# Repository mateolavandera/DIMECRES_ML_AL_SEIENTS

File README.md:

View this project on [CADLAB.io](https://cadlab.io/project/28988). 

# DIMECRES_ML_AL_SEIENTS
## Autors
- Mateo Lavandera Mulet (@mateolavandera)
- Alex Lara Bailon (@AlexLB4)

## Versió - v1.0 ## Curs - Assignatura de Disseny de PCBs amb KiCad - [Curs 2024-2025]

## Objectiu Descripció breu de l'objectiu del projecte.
L’objectiu del nostre projecte és dissenyar un sistema que sigui capaç d'executar correctament les diferents funcions que controlen uns seients elèctrics d’un cotxe qualsevol.

## Requisits i especificacions
→ 3 motors (posició, alçada, reclinació) amb els seus finals de carrera. 
→ Calefacció del seient. 
→ Sensor digital de cinturons. 
→ Memòria externa no volàtil per guardar posicions preprogramades.

## Diagrama de blocs (Afegiu una imatge del diagrama de blocs)
### Tercera versió (final)

## Taula de components
| Descripció | Manufacturer Number | Package | Datasheet | Proveïdor | Unitats |
|------------|--------------------|---------|----------|----------|---------|
| Regulador Lineal 1.5 A  | LD1086V | TO-220 | [Enllaç](https://www.st.com/content/ccc/resource/technical/document/datasheet/53/db/00/58/09/98/4b/36/CD00001884.pdf/files/CD00001884.pdf/jcr:content/translations/en.CD00001884.pdf) | DigiKey | 1 |
| Microcontrolador PIC 8-bit 300mA | PIC18F4580-I/PT | 44-TQFP | [Enllaç](https://ww1.microchip.com/downloads/en/DeviceDoc/39637d.pdf) | DigiKey | 1 |
| DRV Bipolar 4.5-36 V  | L293D | 16-DIP | [Enllaç](https://www.st.com/content/ccc/resource/technical/document/datasheet/04/ac/22/f9/20/5d/43/a1/CD00000059.pdf/files/CD00000059.pdf/jcr:content/translations/en.CD00000059.pdf) | DigiKey | 2 |
| Memòria EEPROM I2C 5 mA  | 24LC512T-I/SN | 8-SOIC | [Enllaç](https://ww1.microchip.com/downloads/en/DeviceDoc/24AA512-24LC512-24FC512-512K-Bit-I2C-Serial-EEPROM-20001754Q.pdf) | DigiKey | 1 |
| Bus CAN (TRANSCEIVER) | TJA1051T	| 8-SOIC | [Enllaç](https://www.nxp.com/docs/en/data-sheet/TJA1051.pdf) | DigiKey | 1 |
| Final de carrera (Comparador) 5 V 4 mA  | LT1721 (Quad) | 16-SOIC | [Enllaç](https://www.analog.com/media/en/technical-documentation/data-sheets/17201fc.pdf) | DigiKey | 1 |
| Condicionador de temperatura (Amplificador) 30 mA  | LT6234 | 16-SSOP | [Enllaç](https://www.analog.com/media/en/technical-documentation/data-sheets/623345fc.pdf) | DigiKey | 1 |
| Sensor de temperatura 60uA | LM35 | 8-SOIC | [Enllaç](https://www.ti.com/lit/ds/symlink/lm35.pdf) | DigiKey | 1 |
| Relé 12mA | Omron G5V-1 | SIP-6 | [Enllaç](https://omronfs.omron.com/en_US/ecb/products/pdf/en-g5v_1.pdf) | DigiKey | 1 |

## Funcionalitats
- [ ] Funció 1
- [ ] Funció 2
- [ ] Funció 3

## Historial de canvis 
| Data | Autor | Branch | Descripció |
|------------|-------|--------|-----------------------------------------------------|
| 2025-03-22 | Alex | `main` | Modificació readme, concretament llistat d'elements |
| 2025-03-22 | Mateo | `main` | Correcció del diagrama de blocs |
| 2025-03-23 | Mateo | `main` | Primera versió de l'esquemàtic  |
| 2025-03-24 | Mateo | `main` | Segona versió de l'esquemàtic  |
| 2025-03-24 | Alex | `main` | Segona versió del llistat d'elements |
| 2025-03-25 | Mateo | `main` | Tercera versió de l'esquemàtic  |
| 2025-03-25 | Alex | `main` | Cuarta versió de l'esquemàtic  |
| 2025-03-25 | Alex | `main` | Segona versió del diagrama de blocs |
| 2025-03-25 | Alex | `main` | Simulacions LTSpice |
| 2025-03-25 | Alex | `main` | Assiganció net clases |
| 2025-03-26 | Alex | `main` | Canvi del comparador, modificació de diagrama i simulacions |
| 2025-03-26 | Mateo | `main` | Cinquena versió de l'esquemàtic |
| 2025-03-29 | Mateo | `main` | Modificació en taula de components: canvi opamp, afegir els sensors i relé |
| 2025-03-29 | Mateo | `main` | Sisena versió de l'esquemàtic |
| 2025-03-29 | Alex | `main` | Tercera versió diagrama de blocs |
| 2025-03-29 | Mateo | `main` | Primera versió prematura de layout |
| 2025-03-30 | Mateo | `main` | Segona versió prematura de layout |
| 2025-03-31 | Mateo | `main` | Tercera versió prematura de layout |
| 2025-03-31 | Mateo | `main` | Setena versió de l'esquemàtic |
| 2025-04-1 | Alex | `main` | Modificació components botonera a l'esquemàtic|
| 2025-04-1 | Alex | `main` | Nova simulació finals de carrera |
| 2025-04-1 | Mateo | `main` | Quarta versió de layout |
| 2025-04-6 | Alex | `main` | Afegir nova botonera a l'esquemàtic |
| 2025-04-7 | Alex | `main` | Cinquena versió layout |
| 2025-04-8 | Alex | `main` | Sisena versió layout |
| 2025-03-31 | Mateo | `main` | Vuitena versió de l'esquemàtic |

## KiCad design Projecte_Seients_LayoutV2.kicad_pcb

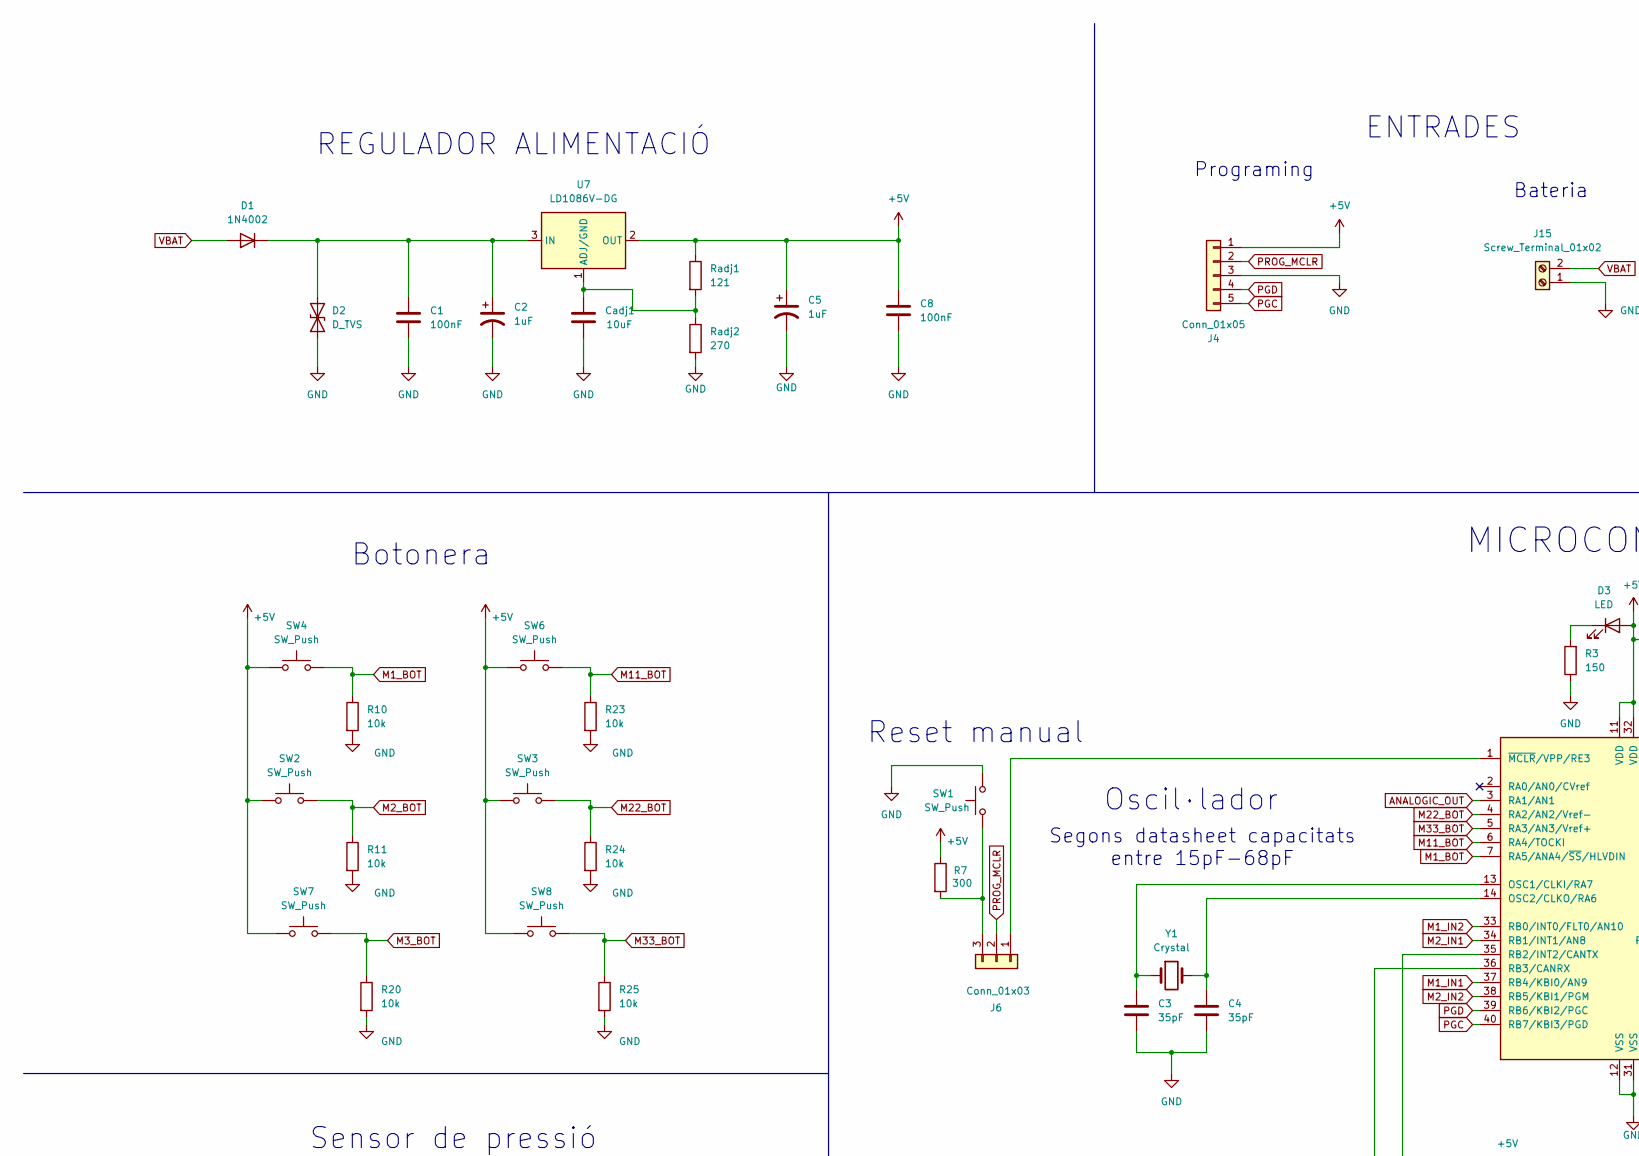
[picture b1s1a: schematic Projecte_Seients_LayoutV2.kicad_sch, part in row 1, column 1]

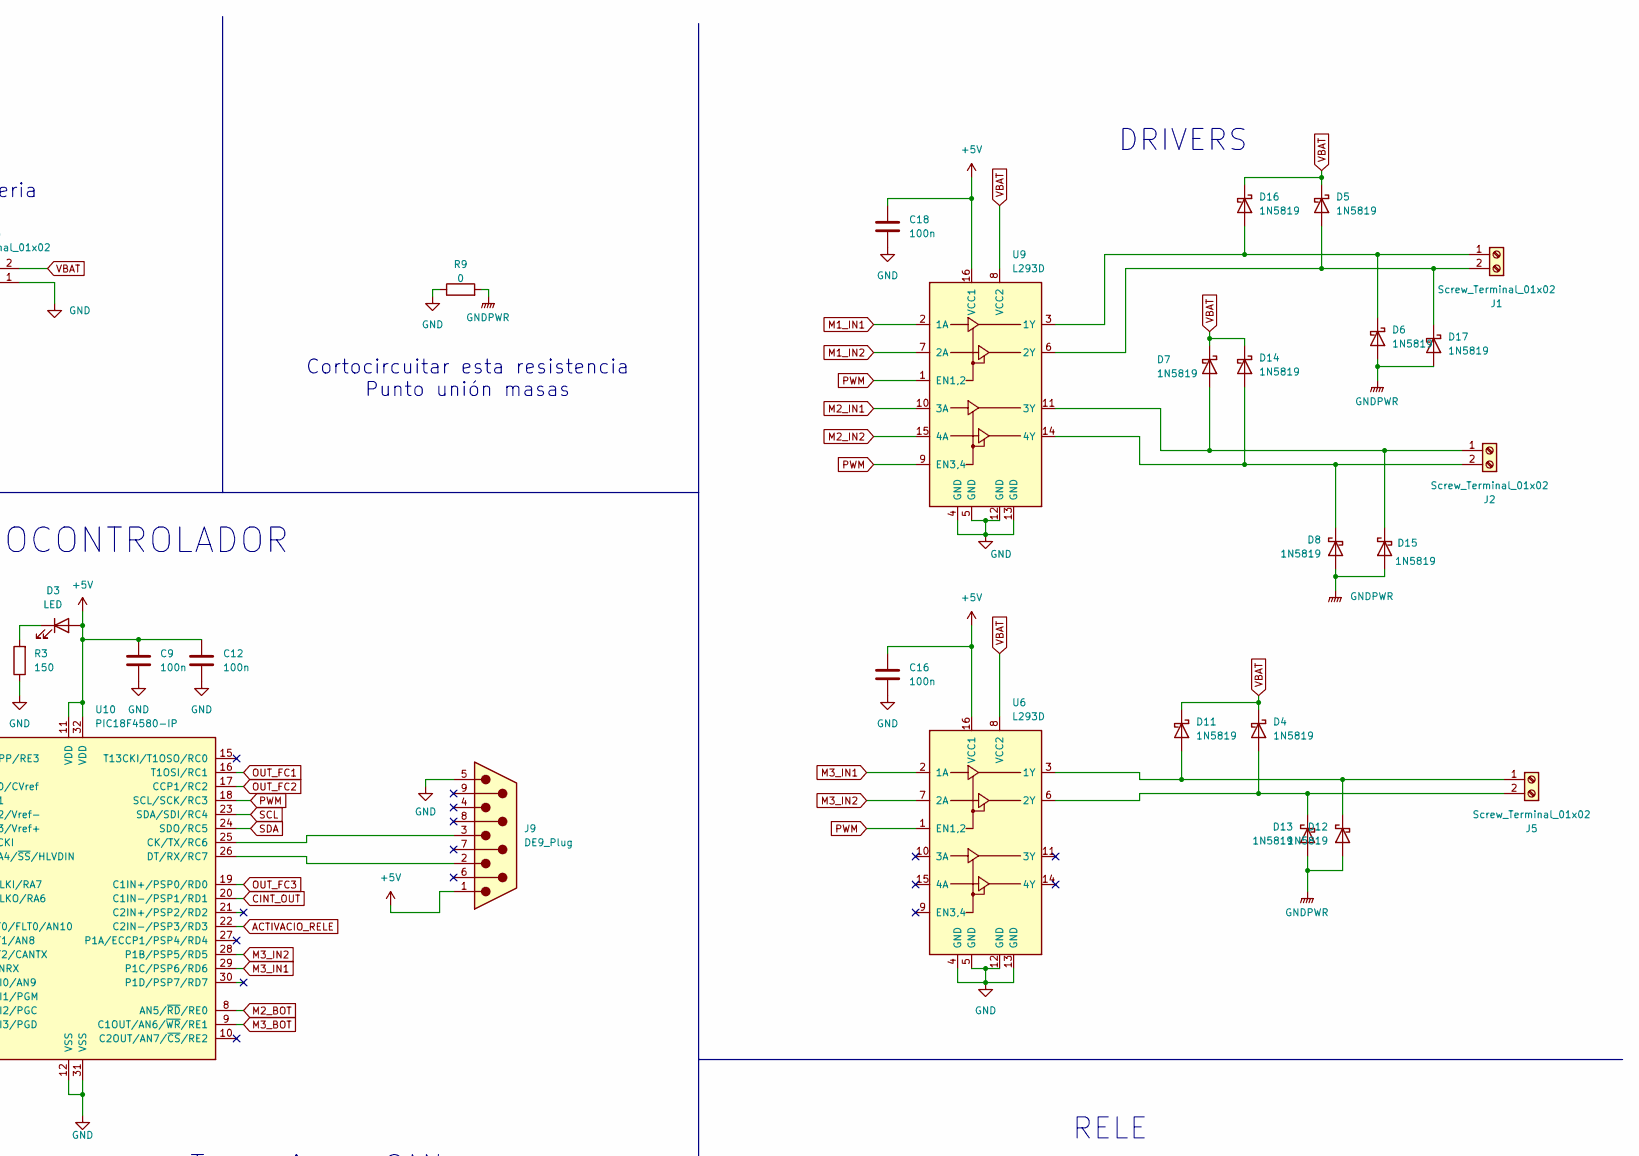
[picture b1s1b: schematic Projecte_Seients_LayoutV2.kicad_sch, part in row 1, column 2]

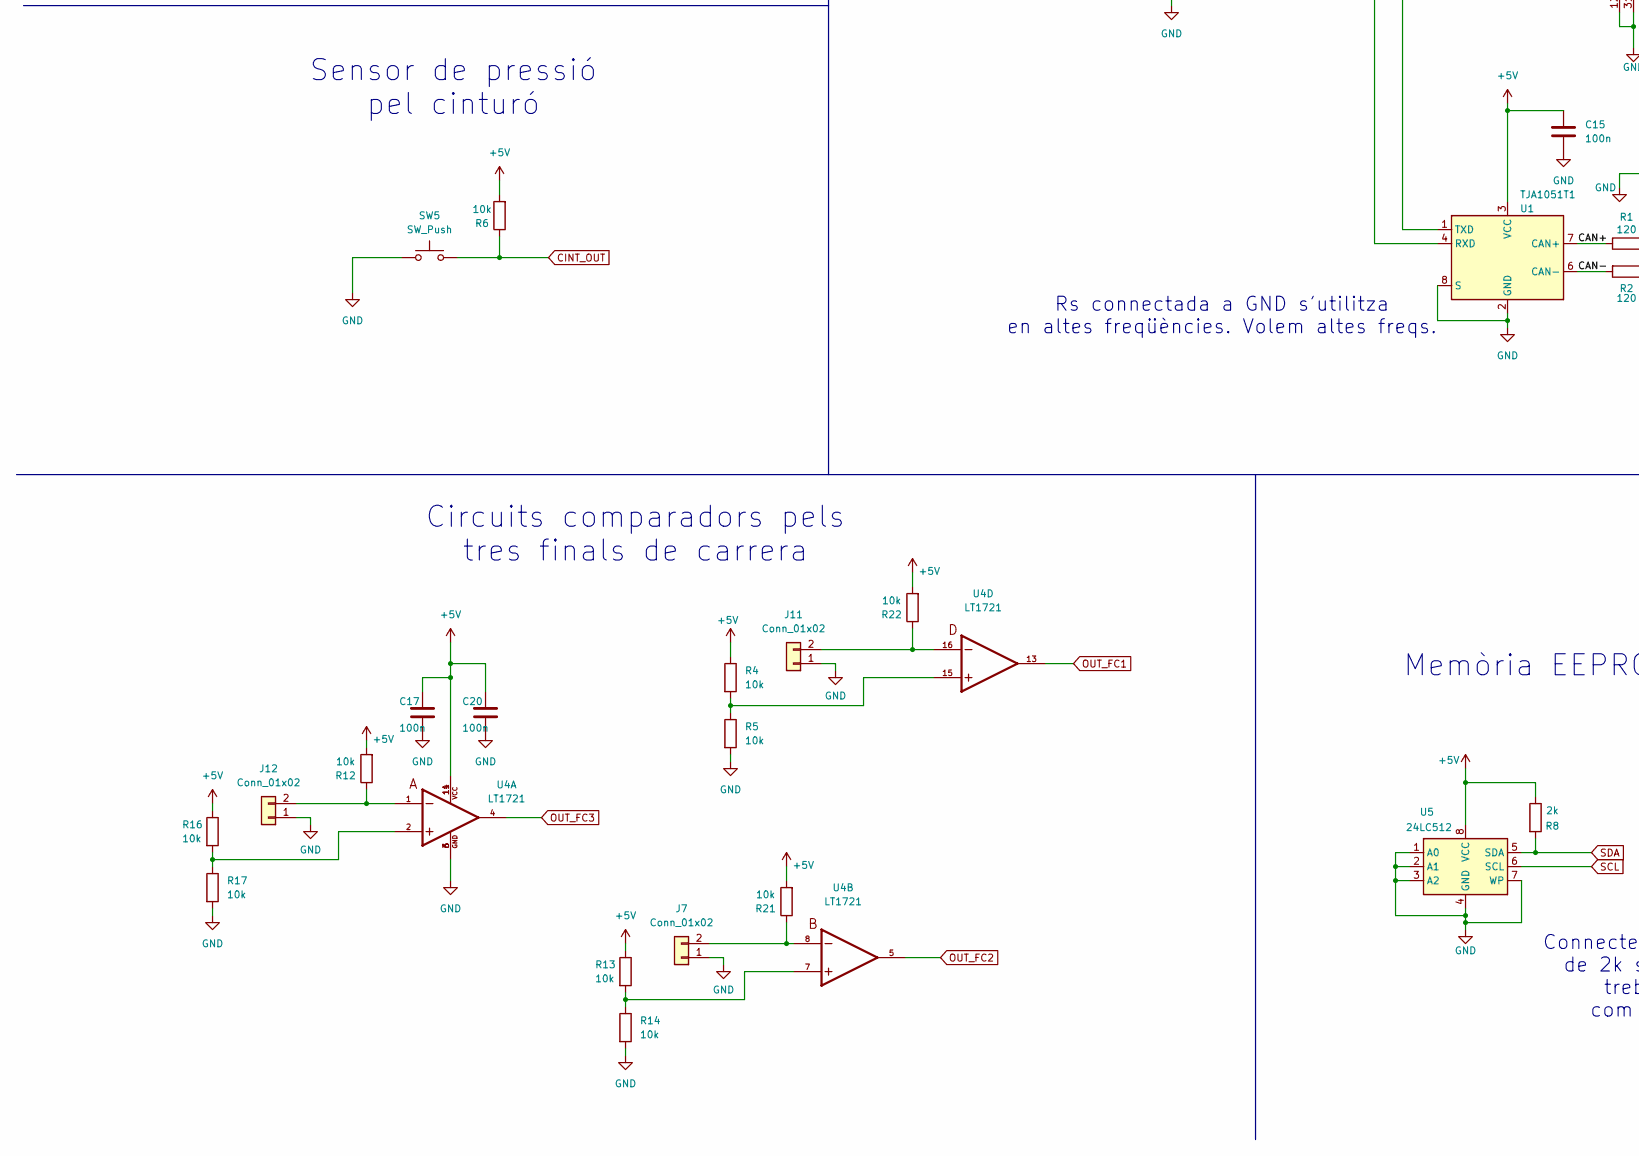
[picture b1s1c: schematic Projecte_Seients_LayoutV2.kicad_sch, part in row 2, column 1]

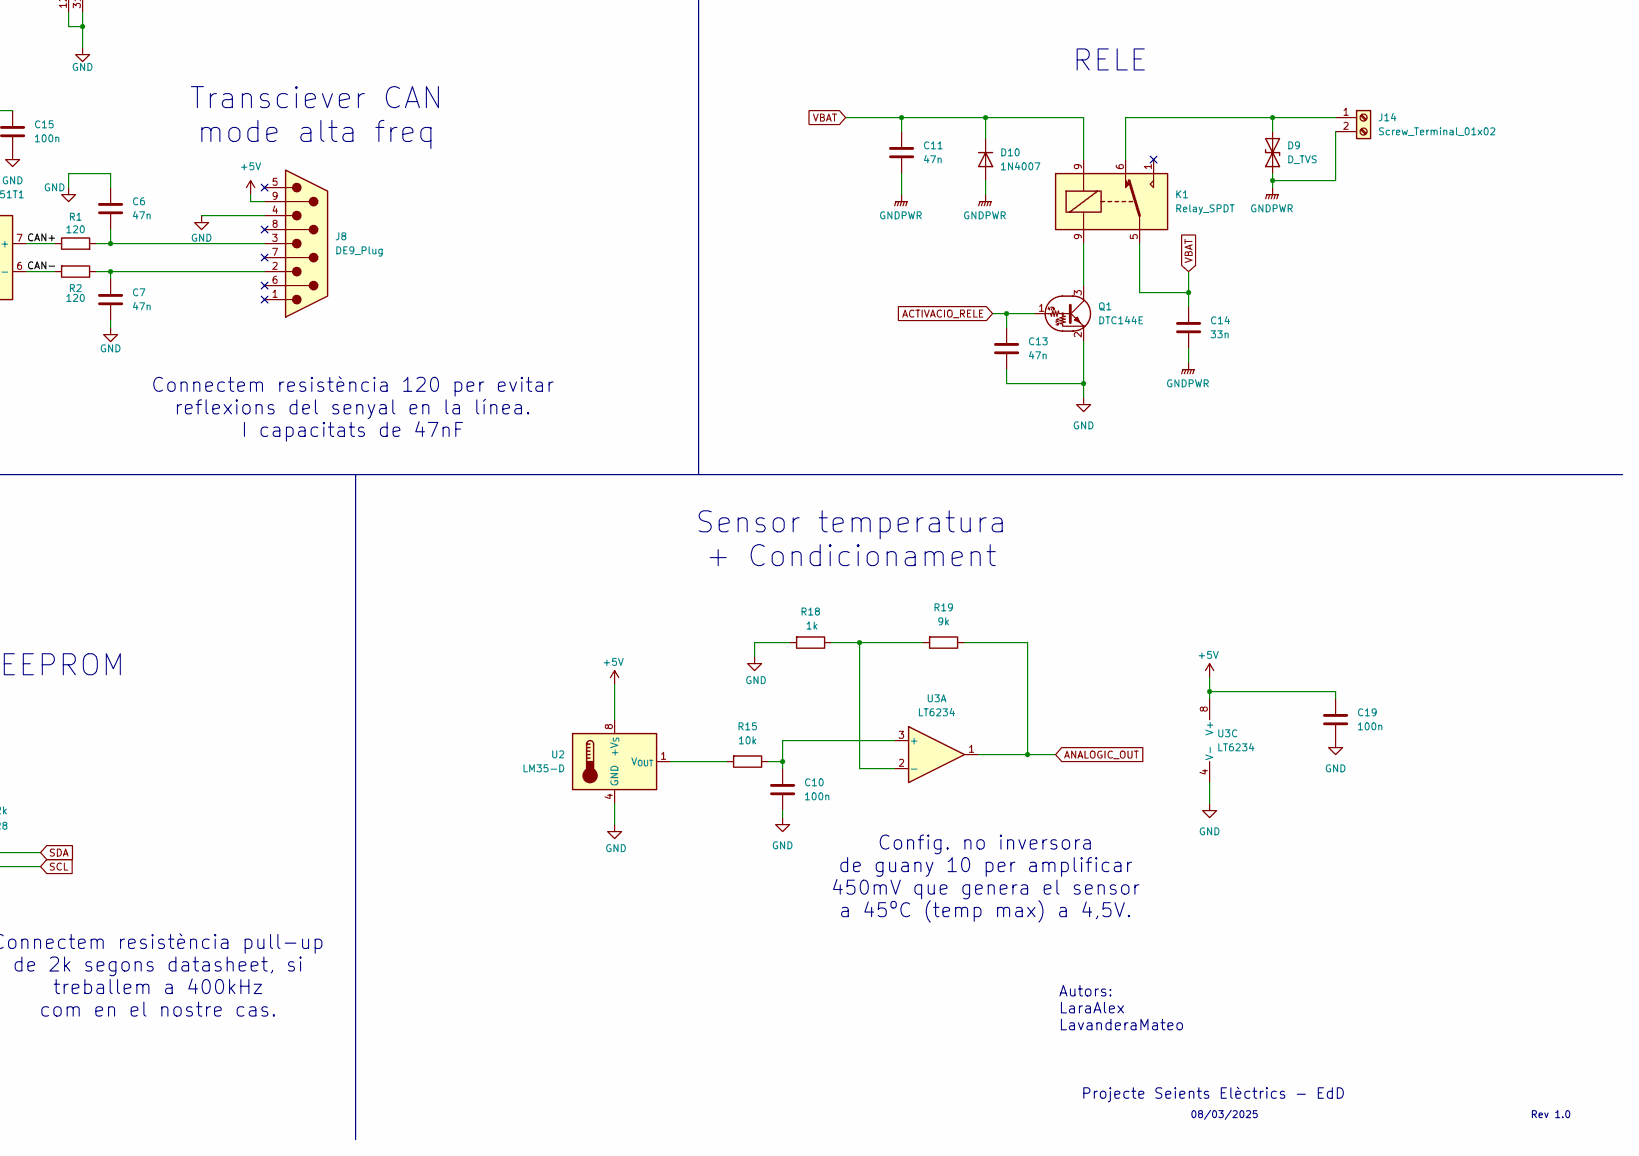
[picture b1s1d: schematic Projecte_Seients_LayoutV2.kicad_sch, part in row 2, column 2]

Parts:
C1, C8: 100nF; C_0805_2012Metric
C2, C5: 1uF; C_Radial_D5.0mm_H5.0mm_P2.00mm
C3, C4: 35pF; C_0805_2012Metric
C6, C7, C11, C13: 47n; C_0805_2012Metric
C9, C10, C12, C15, C16, C17, C18, C19, C20: 100n; C_0805_2012Metric
C14: 33n; C_0805_2012Metric
Cadj1: 10uF; C_0805_2012Metric
D1: 1N4002; D_DO-41_SOD81_P10.16mm_Horizontal
D2, D9: D_TVS; D_DO-41_SOD81_P7.62mm_Horizontal
D3: LED; LED_0805_2012Metric
D4, D5, D6, D7, D8, D11, D12, D13, D14, D15, D16, D17: 1N5819; D_DO-41_SOD81_P10.16mm_Horizontal
D10: 1N4007; D_DO-41_SOD81_P10.16mm_Horizontal
J1, J2, J5, J14, J15: Screw_Terminal_01x02; TerminalBlock_MaiXu_MX126-5.0-02P_1x02_P5.00mm
J4: Conn_01x05; PinHeader_1x05_P2.54mm_Vertical
J6: Conn_01x03; PinHeader_1x03_P2.54mm_Vertical
J7, J11, J12: Conn_01x02; PinHeader_1x02_P2.54mm_Vertical
J8: DE9_Plug; DSUB-9_Male_Horizontal_P2.77x2.84mm_EdgePinOffset9.40mm
J9: DE9_Plug; DSUB-9_Male_Horizontal_P2.77x2.54mm_EdgePinOffset9.40mm
K1: Relay_SPDT; Relay_SPDT_Omron_G5V-1
Q1: DTC144E; TO-220-3_Vertical
R1, R2: 120; R_1206_3216Metric
R3: 150; R_0805_2012Metric
R4, R5, R13, R14, R16, R17: 10k; R_1206_3216Metric
R6, R10, R11, R12, R15, R20, R21, R22, R23, R24, R25: 10k; R_0805_2012Metric
R7: 300; R_1206_3216Metric
R8: 2k; R_1206_3216Metric
R9: 0; R_Axial_DIN0204_L3.6mm_D1.6mm_P5.08mm_Horizontal
R18: 1k; R_0805_2012Metric
R19: 9k; R_0805_2012Metric
Radj1: 121; R_0815_2038Metric
Radj2: 270; R_0815_2038Metric
SW1, SW2, SW3, SW4, SW5, SW6, SW7, SW8: SW_Push; SW_2-1437565-7
TJA1051T1: U1; SOIC-8_3.9x4.9mm_P1.27mm
U2: LM35-D; SOIC-8_3.9x4.9mm_P1.27mm
U3: LT6234; SOIC-8_3.9x4.9mm_P1.27mm
U4: LT1721; SOIC-16_4.55x10.3mm_P1.27mm
U5: 24LC512; SO-8_3.9x4.9mm_P1.27mm
U6, U9: L293D; DIP-16_W7.62mm
U7: LD1086V-DG; HuellaDis
U10: PIC18F4580-IP; DIP-40_W15.24mm_SMD
Y1: Crystal; Crystal_HC49-U_Vertical

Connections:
+5V: C5.1, C8.1, C9.2, C12.2, C15.2, C16.2, C17.2, C18.2, C19.2, C20.2, D3.2 (A), J4.1, J8.9, J9.1, R4.1, R6.2, R7.1, R8.1, R12.2, R13.1, R16.1, R21.2, R22.2, Radj1.1, SW2.1, SW3.1, SW4.1, SW6.1, SW7.1, SW8.1, TJA1051T1.3 (VCC), U2.8 (+V_{S}), U3.8 (V+), U4.11, U4.14, U5.8 (VCC), U6.16 (VCC1), U7.2 (OUT), U9.16 (VCC1), U10.11 (VDD), U10.32 (VDD)
ACTIVACIO_RELE: C13.2, Q1.1 (B), U10.22 (C2IN-/PSP3/RD3)
ANALOGIC_OUT: R19.1, U3.1, U10.3 (RA1/AN1)
CINT_OUT: R6.1, SW5.2, U10.20 (C1IN-/PSP1/RD1)
GND: C1.2, C2.2, C3.2, C4.2, C5.2, C6.1, C7.1, C8.2, C9.1, C10.1, C12.1, C13.1, C15.1, C16.1, C17.1, C18.1, C19.1, C20.1, Cadj1.2, D2.1 (A1), J4.3, J7.1, J8.4, J9.5, J11.1, J12.1, J15.1, Q1.2 (E), R3.1, R5.2, R9.1, R10.2, R11.2, R14.2, R17.2, R18.2, R20.2, R23.2, R24.2, R25.2, Radj2.2, SW1.2, SW5.1, TJA1051T1.2 (GND), TJA1051T1.8 (S), U2.4 (GND), U3.4 (V-), U4.3, U4.6, U5.1 (A0), U5.2 (A1), U5.3 (A2), U5.4 (GND), U5.7 (WP), U6.4 (GND), U6.5 (GND), U6.12 (GND), U6.13 (GND), U9.4 (GND), U9.5 (GND), U9.12 (GND), U9.13 (GND), U10.12 (VSS), U10.31 (VSS)
GNDPWR: C11.1, C14.1, D6.2 (A), D8.2 (A), D9.1 (A1), D10.2 (A), D12.2 (A), D13.2 (A), D15.2 (A), D17.2 (A), J14.2, R9.2
M1_BOT: R10.1, SW4.2, U10.7 (RA5/ANA4/~SS/HLVDIN)
M1_IN1: U9.2 (1A), U10.37 (RB4/KBI0/AN9)
M1_IN2: U9.7 (2A), U10.33 (RB0/INT0/FLT0/AN10)
M2_BOT: R11.1, SW2.2, U10.8 (AN5/~RD/RE0)
M2_IN1: U9.10 (3A), U10.34 (RB1/INT1/AN8)
M2_IN2: U9.15 (4A), U10.38 (RB5/KBI1/PGM)
M3_BOT: R20.1, SW7.2, U10.9 (C1OUT/AN6/~WR/RE1)
M3_IN1: U6.2 (1A), U10.29 (P1C/PSP6/RD6)
M3_IN2: U6.7 (2A), U10.28 (P1B/PSP5/RD5)
M11_BOT: R23.1, SW6.2, U10.6 (RA4/TOCKI)
M22_BOT: R24.1, SW3.2, U10.4 (RA2/AN2/Vref-)
M33_BOT: R25.1, SW8.2, U10.5 (RA3/AN3/Vref+)
unnamed: C6.2, J8.3, R1.2
unnamed: C7.2, J8.2, R2.1
unnamed: C1.1, C2.1, D1.1 (K), D2.2 (A2), U7.3 (IN)
unnamed: D3.1 (K), R3.2
unnamed: D9.2 (A2), J14.1, K1.6
unnamed: D11.2 (A), D12.1 (K), J5.1, U6.3 (1Y)
unnamed: D4.2 (A), D13.1 (K), J5.2, U6.6 (2Y)
unnamed: D8.1 (K), D14.2 (A), J2.2, U9.14 (4Y)
unnamed: D7.2 (A), D15.1 (K), J2.1, U9.11 (3Y)
unnamed: D6.1 (K), D16.2 (A), J1.1, U9.3 (1Y)
unnamed: D5.2 (A), D17.1 (K), J1.2, U9.6 (2Y)
unnamed: J6.1, U10.1 (~MCLR/VPP/RE3)
unnamed: J6.3, R7.2, SW1.1
unnamed: J7.2, R21.1, U4.8
unnamed: J11.2, R22.1, U4.16
unnamed: J12.2, R12.1, U4.1
unnamed: R4.2, R5.1, U4.15
unnamed: R13.2, R14.1, U4.7
unnamed: R16.2, R17.1, U4.2
unnamed: R1.1, TJA1051T1.7 (CAN+)
unnamed: R2.2, TJA1051T1.6 (CAN-)
unnamed: TJA1051T1.4 (RXD), U10.36 (RB3/CANRX)
unnamed: TJA1051T1.1 (TXD), U10.35 (RB2/INT2/CANTX)
unnamed: R15.2, U2.1 (V_{OUT})
unnamed: C10.2, R15.1, U3.3 (+)
unnamed: R18.1, R19.2, U3.2 (-)
unnamed: Cadj1.1, Radj1.2, Radj2.1, U7.1 (ADJ/GND)
unnamed: J9.3, U10.25 (CK/TX/RC6)
unnamed: J9.2, U10.26 (DT/RX/RC7)
unnamed: C3.1, U10.13 (OSC1/CLKI/RA7), Y1.1
unnamed: C4.1, U10.14 (OSC2/CLKO/RA6), Y1.2
OUT_FC1: U4.13, U10.16 (T1OSI/RC1)
OUT_FC2: U4.5, U10.17 (CCP1/RC2)
OUT_FC3: U4.4, U10.19 (C1IN+/PSP0/RD0)
PGC: J4.5, U10.40 (RB7/KBI3/PGD)
PGD: J4.4, U10.39 (RB6/KBI2/PGC)
PROG_MCLR: J4.2, J6.2
PWM: U6.1 (EN1,2), U9.1 (EN1,2), U9.9 (EN3,4), U10.18 (SCL/SCK/RC3)
SCL: U5.6 (SCL), U10.23 (SDA/SDI/RC4)
SDA: R8.2, U5.5 (SDA), U10.24 (SDO/RC5)

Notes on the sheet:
Segons datasheet capacitats entre 15pF-68pF
Bateria
Transciever CAN mode alta freq
Connectem resistència pull-up de 2k segons datasheet, si treballem a 400kHz com en el nostre cas.
Sensor temperatura + Condicionament
Programing
Cortocircuitar esta resistencia Punto unión masas
Projecte Seients Elèctrics - EdD
Sensor de pressió pel cinturó
Autors: LaraAlex LavanderaMateo
Rs connectada a GND s'utilitza en altes freqüències. Volem altes freqs.
REGULADOR ALIMENTACIÓ
Botonera
Circuits comparadors pels tres finals de carrera
Rev 1.0
08/03/2025
Memòria EEPROM
RELE
Reset manual
Oscil·lador
Config. no inversora de guany 10 per amplificar 450mV que genera el sensor a 45ºC (temp max) a 4,5V.
ENTRADES
Connectem resistència 120 per evitar reflexions del senyal en la línea. I capacitats de 47nF
MICROCONTROLADOR
DRIVERS

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
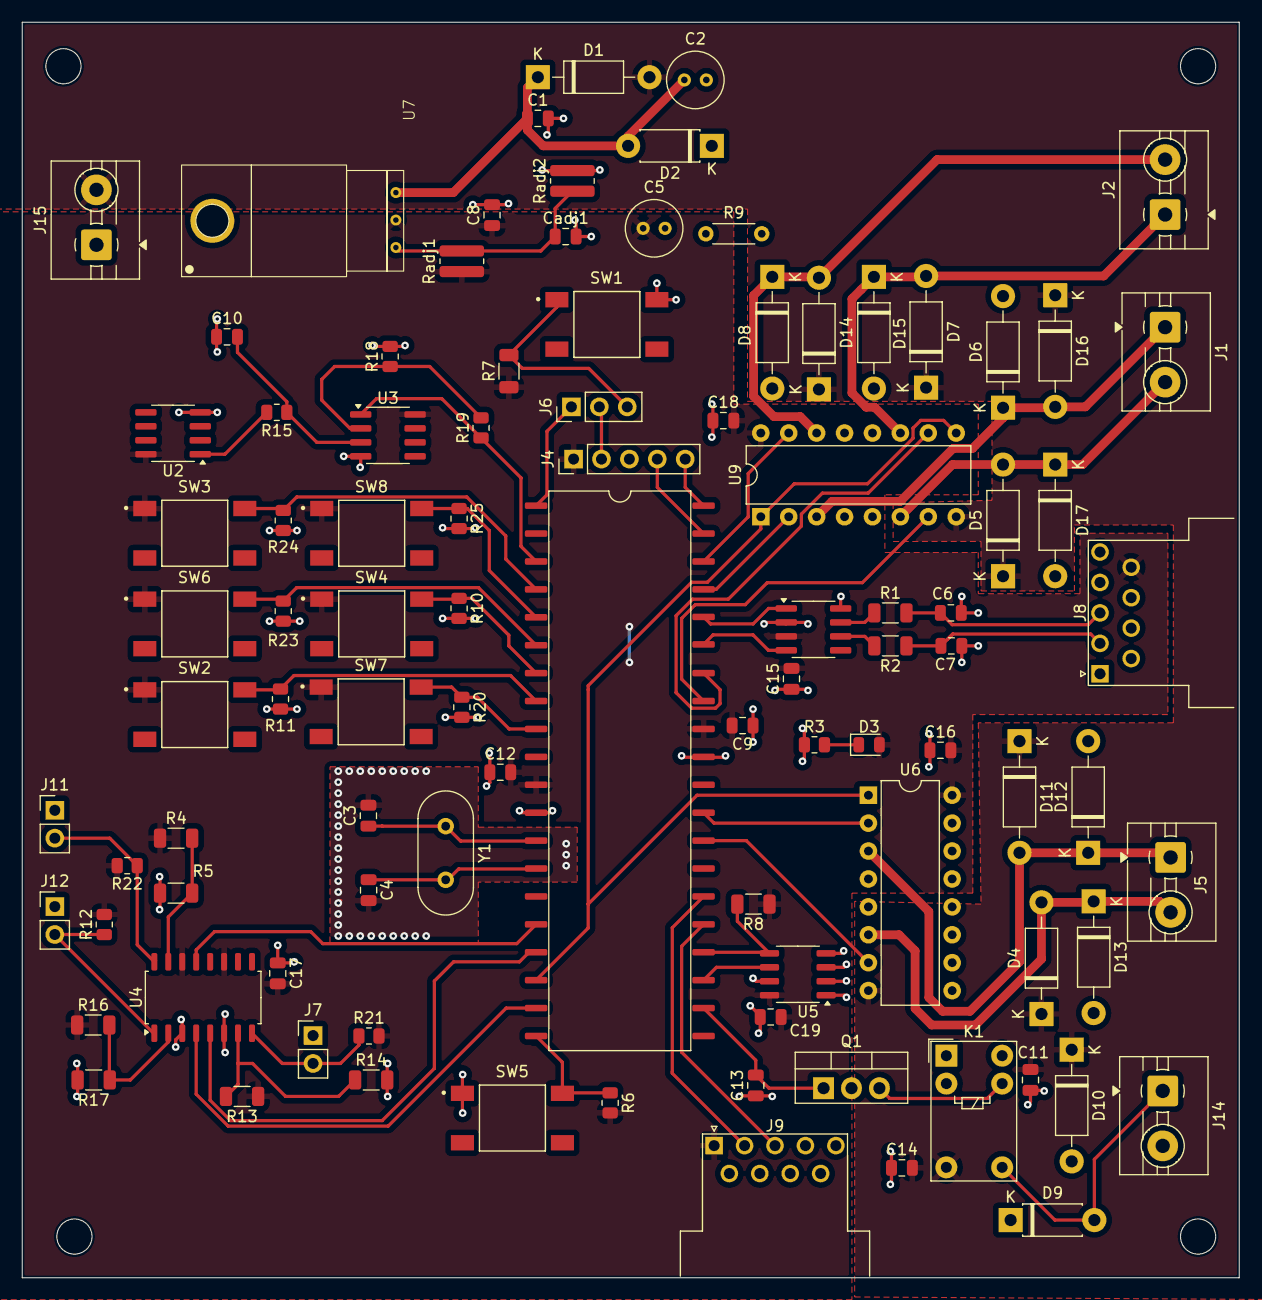
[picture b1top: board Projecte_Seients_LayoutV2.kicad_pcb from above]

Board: 2 copper layers, 110.8 x 114.2 mm, 96 parts (0 on the bottom side), 60 nets.

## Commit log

2025-03-22 Backlink to CADLAB.io has been added.
2025-03-25 Update README.md
    Acepta esta propuesta primero
